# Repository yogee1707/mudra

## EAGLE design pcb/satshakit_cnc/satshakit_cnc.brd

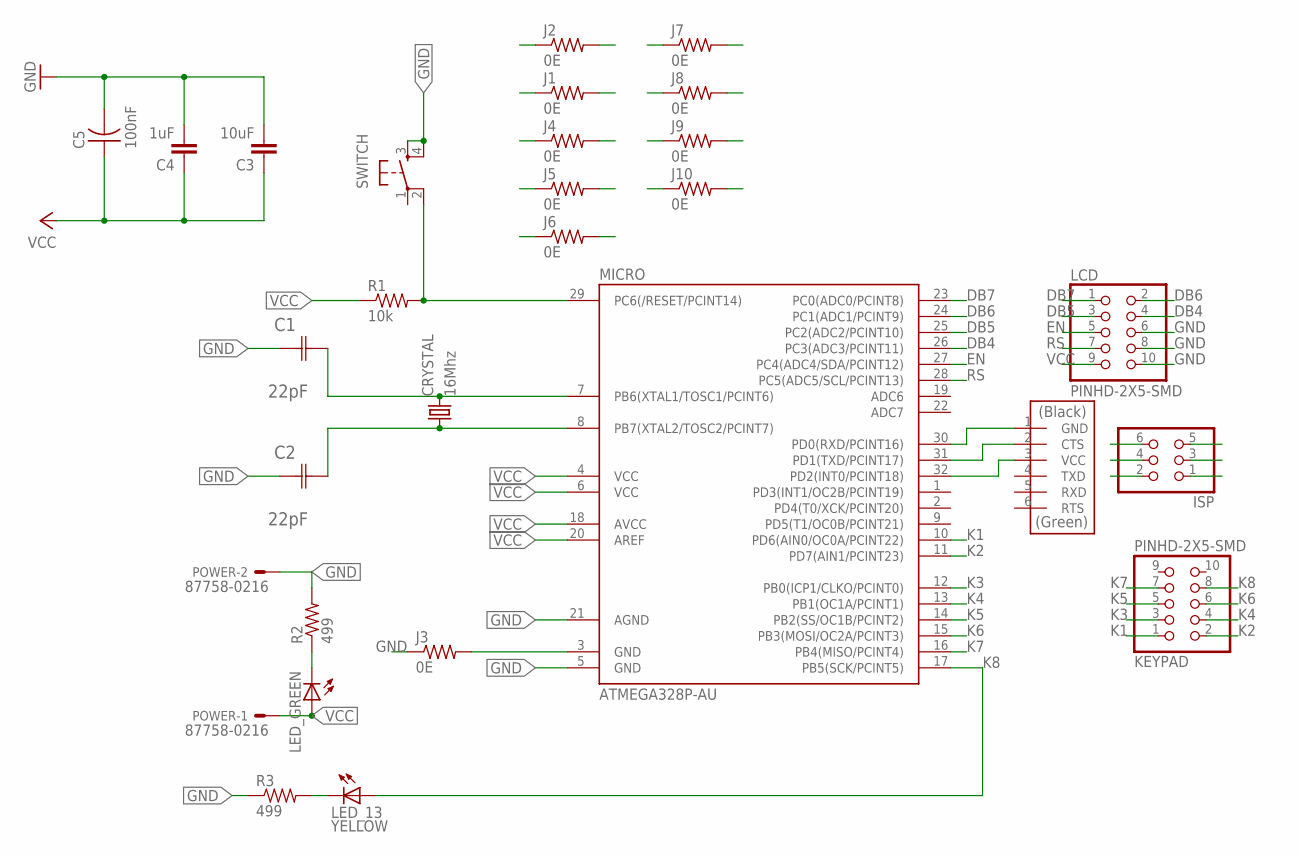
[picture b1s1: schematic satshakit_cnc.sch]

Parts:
C1, C2: 22pF; CAPC3216X178N
C3: 10uF; 1206
C4: 1uF; 1206
C5: 100nF; C1206FAB
CRYSTAL: 16Mhz; CSM-7X-DU
GSM: FTDI-SMD-HEADER; 1X06SMD
ISP: PINHD-2X3-SMD; 2X03SMD
J1, J2, J3, J4, J5, J6, J7, J8, J9, J10: 0E; R1206FAB
KEYPAD: PINHD-2X5-SMD; 2X05SMD
LCD: PINHD-2X5-SMD; 2X05SMD
LED_13: YELLOW; 1206
LED_GREEN: LED1206; 1206
MICRO: ATMEGA328P-AU; TQFP32-08
POWER: 87758-0216
R1: 10k; 1206
R2, R3: 499; 1206
SWITCH: 6MM_SWITCH6MM_SWITCH; 6MM_SWITCH

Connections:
DB4: LCD.4, MICRO.26 (PC3(ADC3/PCINT11))
DB5: LCD.3, MICRO.25 (PC2(ADC2/PCINT10))
DB6: LCD.2, MICRO.24 (PC1(ADC1/PCINT9))
DB7: LCD.1, MICRO.23 (PC0(ADC0/PCINT8))
EN: LCD.5, MICRO.27 (PC4(ADC4/SDA/PCINT12))
GND: C1.1 (C1), C2.1 (C1), C3.2, C4.2, C5.2, ISP.6, J3.1, J3.2, J8.1, J8.2, J10.1, J10.2, LCD.6, LCD.8, LCD.10, MICRO.3 (GND), MICRO.5 (GND), MICRO.21 (AGND), POWER.2, R2.2, R3.1, SWITCH.3 (S), SWITCH.4 (S1)
K1: KEYPAD.1, MICRO.10 (PD6(AIN0/OC0A/PCINT22))
K2: KEYPAD.2, MICRO.11 (PD7(AIN1/PCINT23))
K3: KEYPAD.3, MICRO.12 (PB0(ICP1/CLKO/PCINT0))
K4: KEYPAD.4, MICRO.13 (PB1(OC1A/PCINT1))
K5: KEYPAD.5, MICRO.14 (PB2(SS/OC1B/PCINT2))
K6: ISP.4, KEYPAD.6, MICRO.15 (PB3(MOSI/OC2A/PCINT3))
K7: ISP.1, J5.1, J5.2, KEYPAD.7, MICRO.16 (PB4(MISO/PCINT4))
K8: ISP.3, J4.1, J4.2, KEYPAD.8, LED_13.1 (A), MICRO.17 (PB5(SCK/PCINT5))
unnamed: GSM.1 (GND), MICRO.30 (PD0(RXD/PCINT16))
unnamed: C1.2 (C2), CRYSTAL.2, MICRO.7 (PB6(XTAL1/TOSC1/PCINT6))
unnamed: GSM.2 (CTS), MICRO.31 (PD1(TXD/PCINT17))
unnamed: GSM.3 (VCC), MICRO.32 (PD2(INT0/PCINT18))
unnamed: C2.2 (C2), CRYSTAL.1, MICRO.8 (PB7(XTAL2/TOSC2/PCINT7))
unnamed: LED_GREEN.2 (C), R2.1
unnamed: LED_13.2 (C), R3.2
RS: LCD.7, MICRO.28 (PC5(ADC5/SCL/PCINT13))
RST: ISP.5, J1.1, J1.2, J9.1, J9.2, MICRO.29 (PC6(/RESET/PCINT14)), R1.2, SWITCH.2 (P1)
VCC: C3.1, C4.1, C5.1, ISP.2, J2.1, J2.2, J6.1, J6.2, J7.1, J7.2, LCD.9, LED_GREEN.1 (A), MICRO.4 (VCC), MICRO.6 (VCC), MICRO.18 (AVCC), MICRO.20 (AREF), POWER.1, R1.1

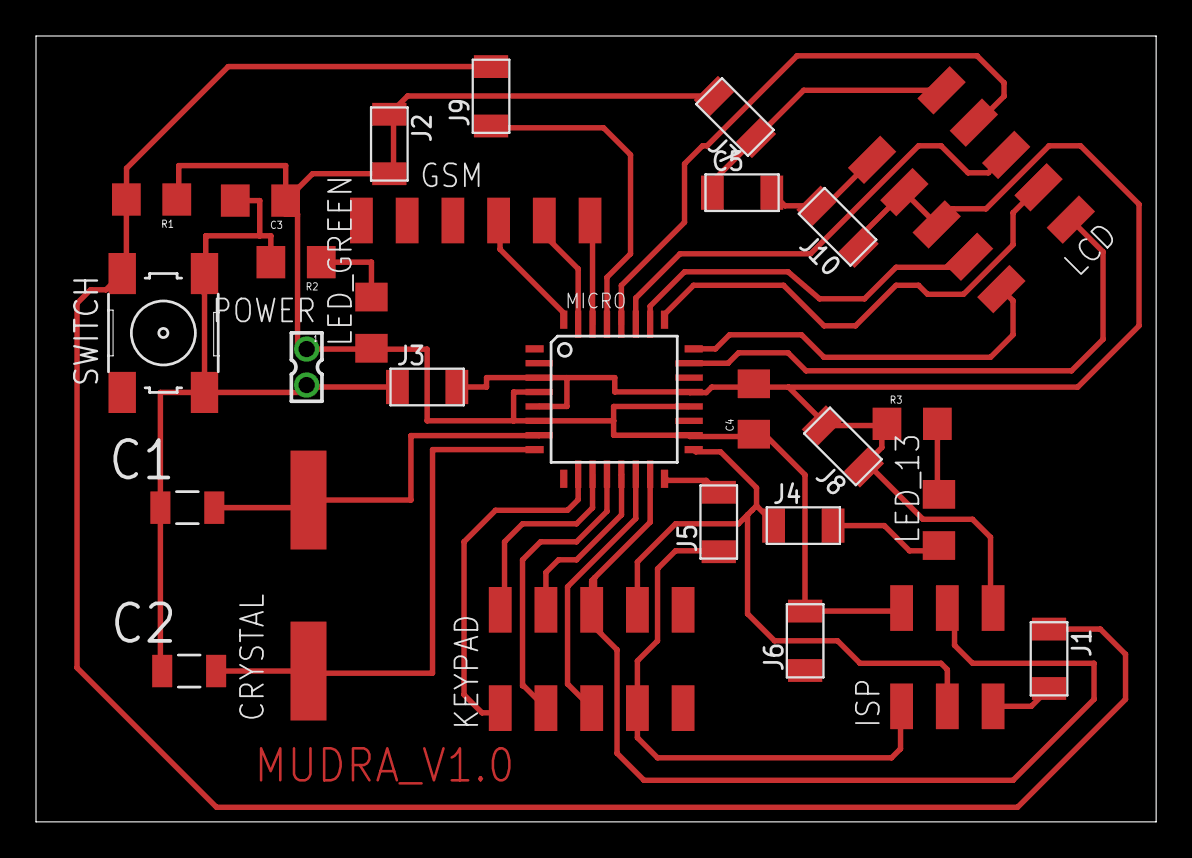
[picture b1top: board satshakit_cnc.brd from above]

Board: 2 copper layers, 62.2 x 43.7 mm, 28 parts (0 on the bottom side), 24 nets.

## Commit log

2016-07-06 Update LICENSE
2016-07-06 yogee uplodaing fab2016 final project
2016-07-09 adding pcbs
2016-07-09 adding photos & stickers

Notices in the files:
parts and their libraries:
01_SparkFun: Licensing: CC v3.0 Share-Alike You are welcome to use this library for commercial purposes.
